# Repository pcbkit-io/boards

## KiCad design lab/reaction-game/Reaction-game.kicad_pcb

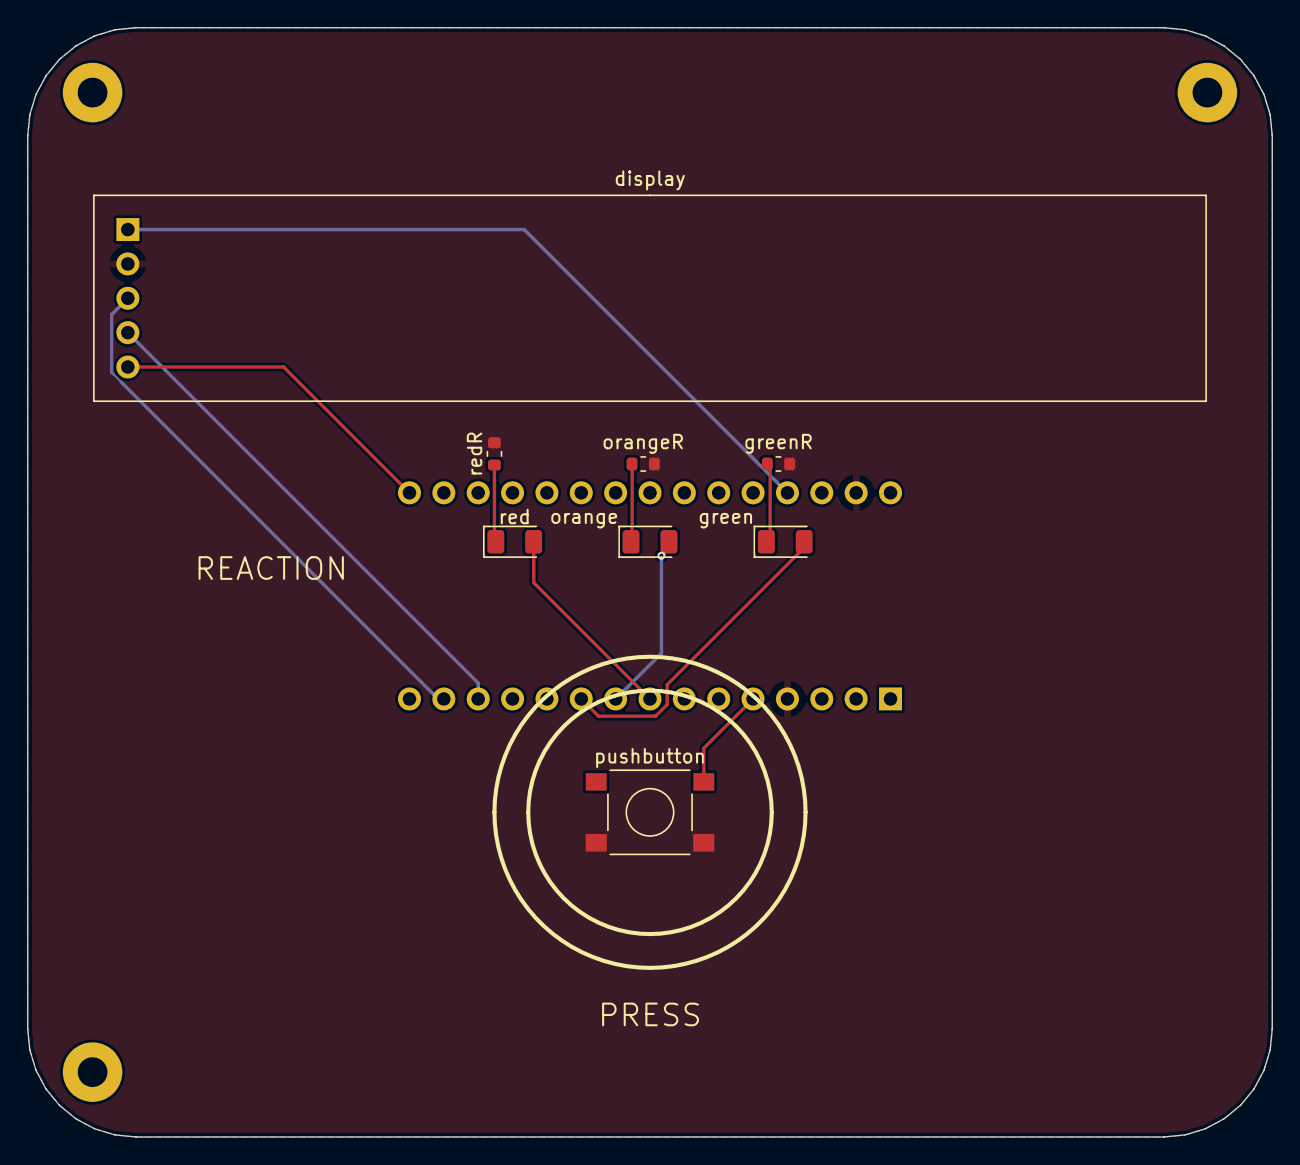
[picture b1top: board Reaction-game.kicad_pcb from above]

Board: 2 copper layers, 92.0 x 82.0 mm, 12 parts (1 on the bottom side), 12 nets.

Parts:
H1, H2, H3: MountingHole_2.2mm_M2_Pad
U1: A000005; Arduino_Nano_Socket_2x15_P2.54mm_W15.24mm
display: MAX7219 8-digit 7-segment LED display module; MAX7219_8digit_Module_Socket_1x05_P2.54mm
green: green; LED_1206_3216Metric
greenR: 1kohm; R_0603_1608Metric
orange: orange; LED_1206_3216Metric
orangeR: 1kohm; R_0603_1608Metric
pushbutton: PTS645SM43SMTR92 LFS; SW_Tactile_SPST_6x6mm_SMD
red: red; LED_1206_3216Metric
redR: 1kohm; R_0603_1608Metric

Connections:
GND: U1.4 (GND), U1.29 (GND), display.2 (GND), greenR.2 (b), orangeR.2 (b), pushbutton.2 (b), redR.2 (b)
GREEN: U1.10 (D7), green.2 (A)
GREEN_K: green.1 (K), greenR.1 (a)
LOAD: U1.13 (D10), display.4 (CS)
MOSI: U1.14 (D11), display.3 (DIN)
ORANGE: U1.9 (D6), orange.2 (A)
ORANGE_K: orange.1 (K), orangeR.1 (a)
PRESS: U1.5 (D2), pushbutton.1 (a)
RED: U1.8 (D5), red.2 (A)
RED_K: red.1 (K), redR.1 (a)
SCK: U1.16 (D13), display.5 (CLK)
V5: U1.27 (P5V), display.1 (VCC)

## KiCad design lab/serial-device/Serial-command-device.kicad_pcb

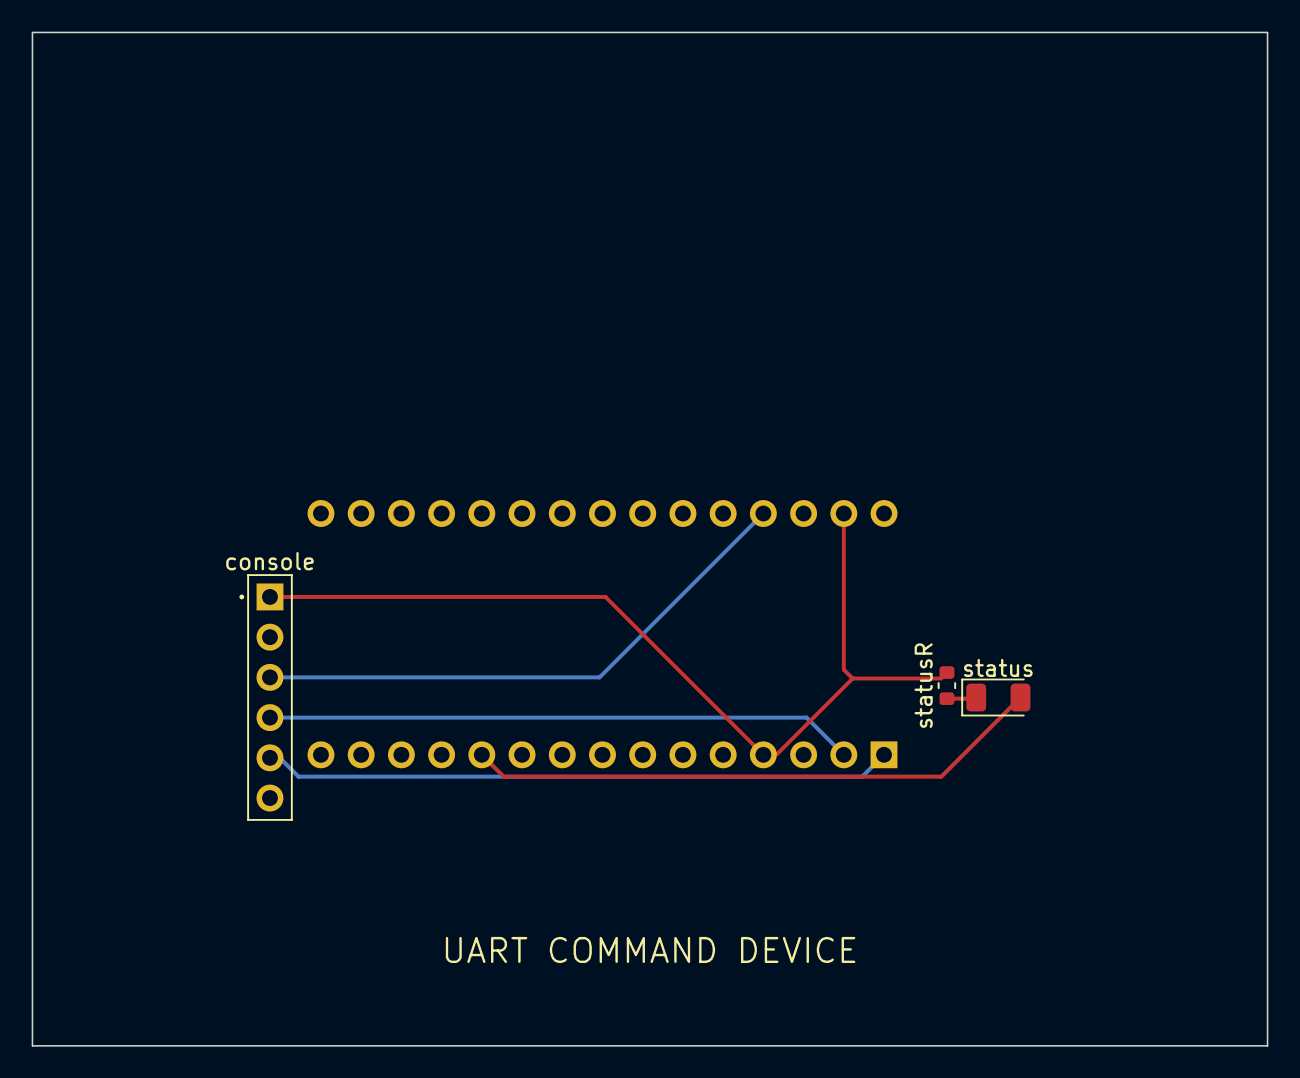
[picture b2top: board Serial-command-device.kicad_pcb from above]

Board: 2 copper layers, 78.0 x 64.0 mm, 4 parts (1 on the bottom side), 6 nets.

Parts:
U1: A000005; Arduino_Nano_Socket_2x15_P2.54mm_W15.24mm
console: PinHeader_1x06_P2.54mm_Vertical
status: green; LED_1206_3216Metric
statusR: 1kohm; R_0603_1608Metric

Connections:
GND: U1.4 (GND), U1.29 (GND), console.1, statusR.2 (b)
LIGHT: U1.11 (D8), status.2 (A)
LIGHT_K: status.1 (K), statusR.1 (a)
RX: U1.2 (D0), console.4
TX: U1.1 (D1), console.5
V5: U1.27 (P5V), console.3

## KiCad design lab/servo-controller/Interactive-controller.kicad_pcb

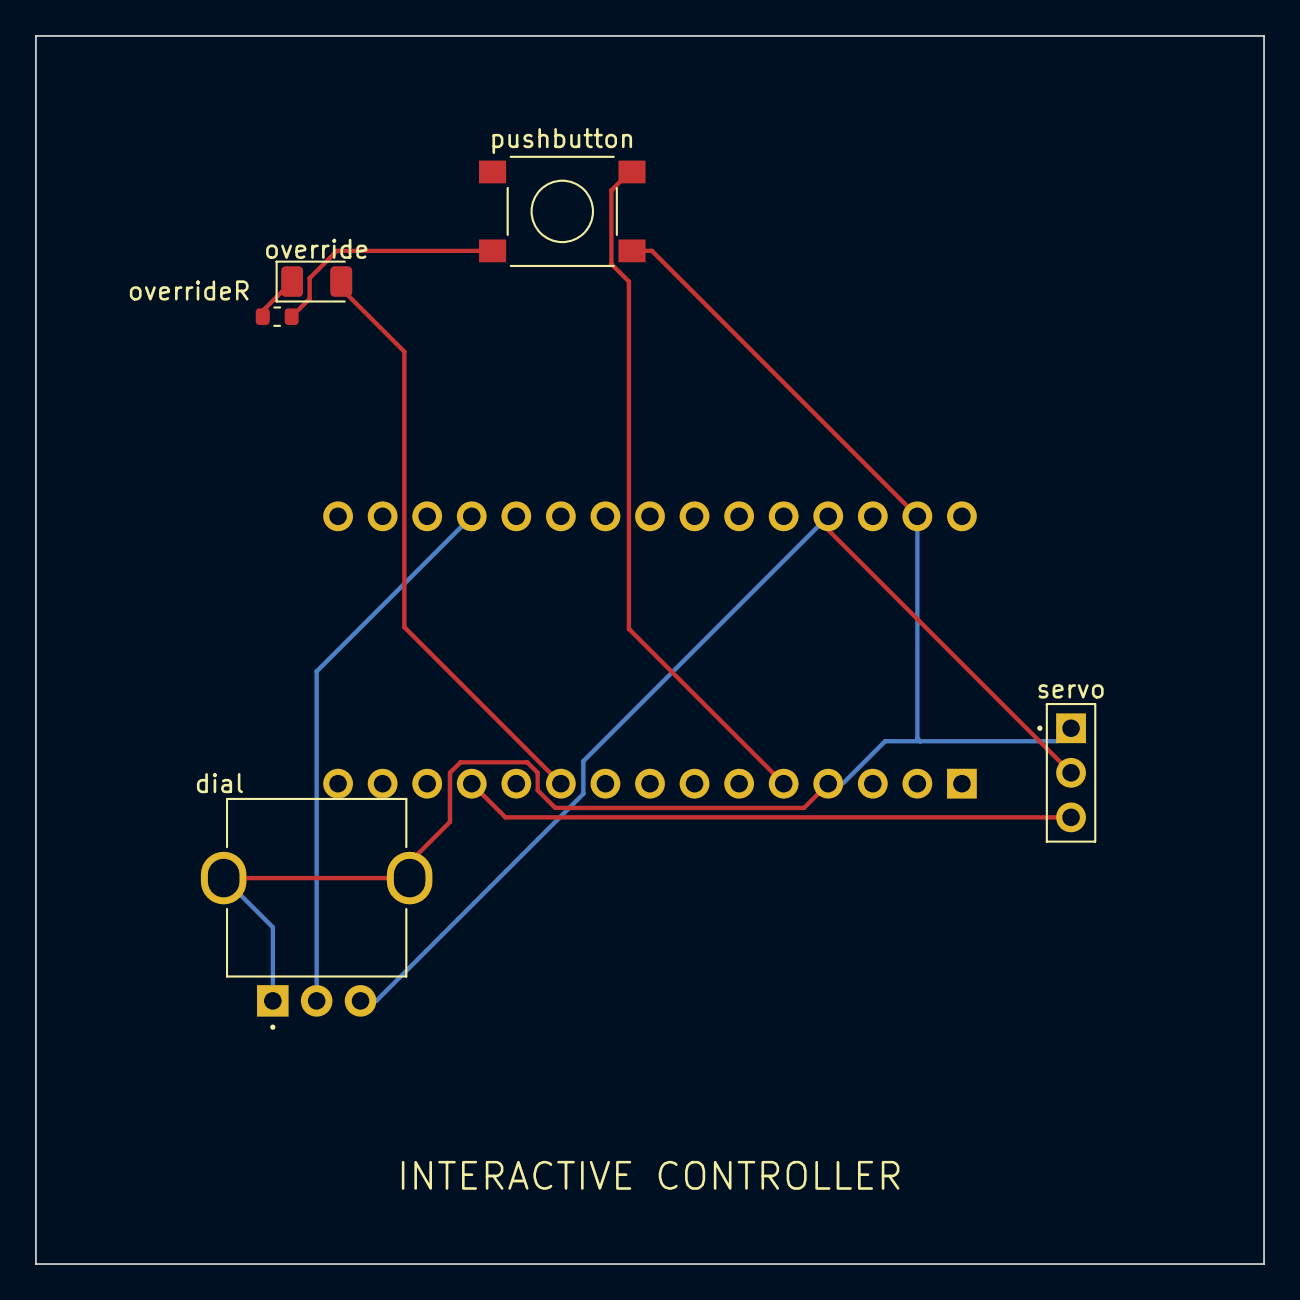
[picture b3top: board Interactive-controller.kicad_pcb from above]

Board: 2 copper layers, 70.0 x 70.0 mm, 6 parts (1 on the bottom side), 7 nets.

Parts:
U1: A000005; Arduino_Nano_Socket_2x15_P2.54mm_W15.24mm
dial: PTV09A-4020F-B103; Potentiometer_Bourns_PTV09A-4_Vertical
override: green; LED_1206_3216Metric
overrideR: 1kohm; R_0603_1608Metric
pushbutton: PTS645SM43SMTR92 LFS; SW_Tactile_SPST_6x6mm_SMD
servo: RC servo header, 1 x 3 pins, 2.54 mm; PinHeader_1x03_P2.54mm_Vertical

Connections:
ANALOG: U1.19 (A0), dial.2 (W)
BUTTON: U1.5 (D2), pushbutton.1 (a)
GND: U1.4 (GND), U1.29 (GND), dial.1 (CCW), dial.MP, overrideR.1 (a), pushbutton.2 (b), servo.1 (GND)
OVERRIDE: U1.10 (D7), override.2 (A)
OVERRIDE_K: override.1 (K), overrideR.2 (b)
SERVO: U1.12 (D9), servo.3 (SIG)
V5: U1.27 (P5V), dial.3 (CW), servo.2 (VPLUS)

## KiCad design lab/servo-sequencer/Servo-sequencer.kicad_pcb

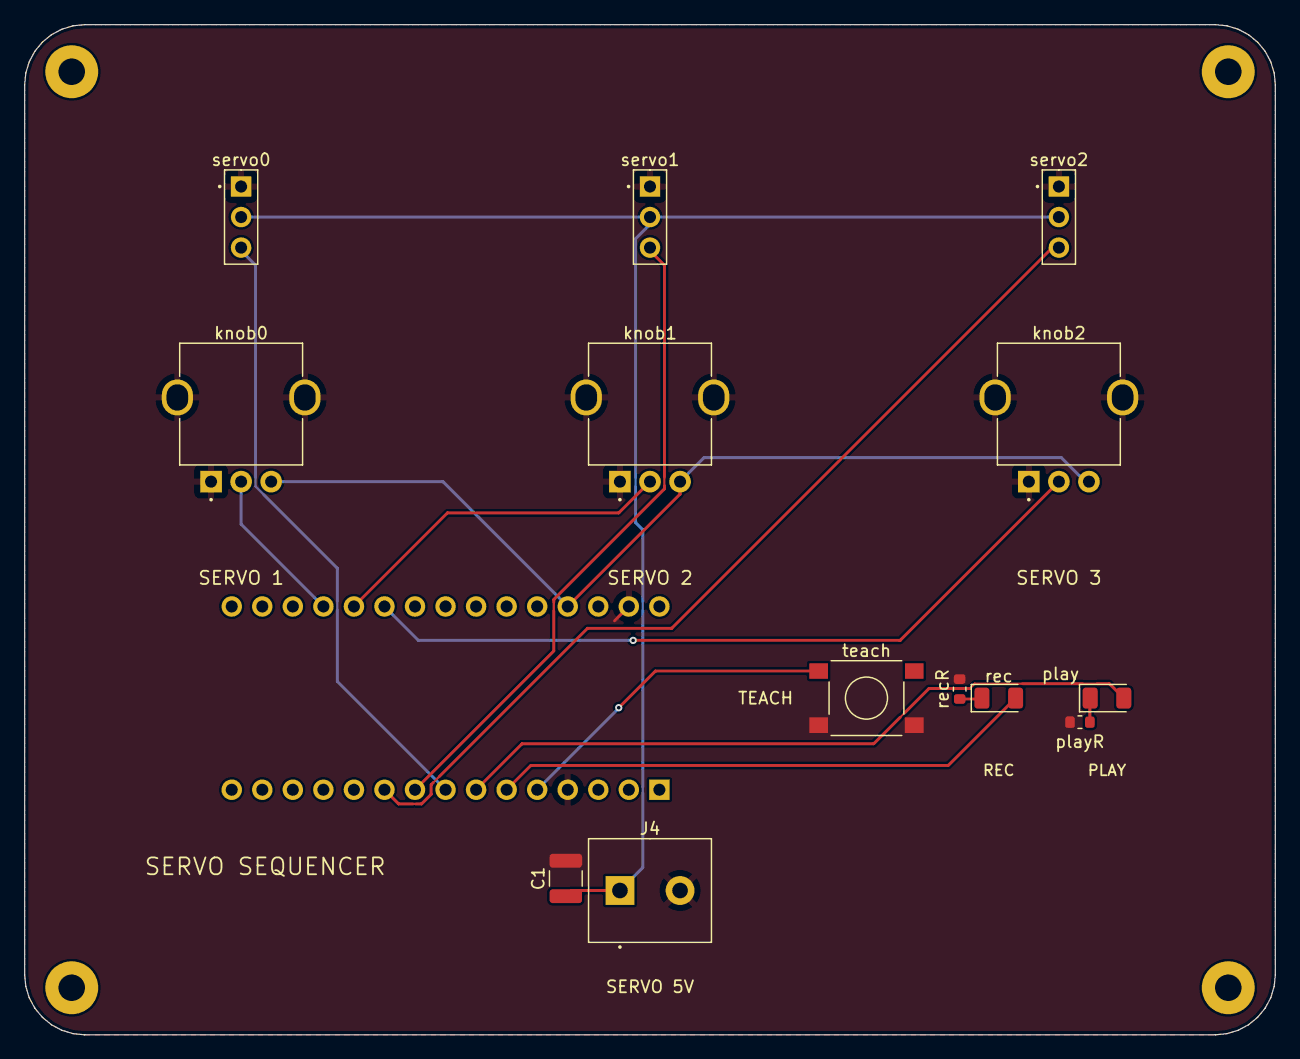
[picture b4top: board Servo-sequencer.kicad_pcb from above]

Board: 2 copper layers, 104.0 x 84.0 mm, 18 parts (1 on the bottom side), 14 nets.

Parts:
C1: 100uF; C_1210_3225Metric
H1, H2, H3, H4: MountingHole_2.2mm_M2_Pad
J4: 5 V 2 A; TerminalBlock_1x02_P5.00mm
U1: A000005; Arduino_Nano_Socket_2x15_P2.54mm_W15.24mm
knob0, knob1, knob2: PTV09A-4020F-B103; Potentiometer_Bourns_PTV09A-4_Vertical
play: green; LED_1206_3216Metric
playR: 1kohm; R_0603_1608Metric
rec: red; LED_1206_3216Metric
recR: 1kohm; R_0603_1608Metric
servo0, servo1, servo2: RC servo header, 1 x 3 pins, 2.54 mm; PinHeader_1x03_P2.54mm_Vertical
teach: PTS645SM43SMTR92 LFS; SW_Tactile_SPST_6x6mm_SMD

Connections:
GND: C1.2 (b), J4.2, U1.4 (GND), U1.29 (GND), knob0.1 (CCW), knob0.MP, knob1.1 (CCW), knob1.MP, knob2.1 (CCW), knob2.MP, playR.2 (b), recR.2 (b), servo0.1 (GND), servo1.1 (GND), servo2.1 (GND), teach.2 (b)
KNOB0: U1.19 (A0), knob0.2 (W)
KNOB1: U1.20 (A1), knob1.2 (W)
KNOB2: U1.21 (A2), knob2.2 (W)
PLAY: U1.7 (D4), play.2 (A)
PLAY_K: play.1 (K), playR.1 (a)
REC: U1.6 (D3), rec.2 (A)
REC_K: rec.1 (K), recR.1 (a)
SERVO0: U1.8 (D5), servo0.3 (SIG)
SERVO1: U1.9 (D6), servo1.3 (SIG)
SERVO2: U1.10 (D7), servo2.3 (SIG)
TEACH: U1.5 (D2), teach.1 (a)
V5: U1.27 (P5V), knob0.3 (CW), knob1.3 (CW), knob2.3 (CW)
VSERVO: C1.1 (a), J4.1, servo0.2 (VPLUS), servo1.2 (VPLUS), servo2.2 (VPLUS)

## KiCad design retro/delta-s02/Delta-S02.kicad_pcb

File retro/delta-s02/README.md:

# Delta-S02

**Дельта-С-02**, the ZX Spectrum 48K compatible home computer made by Elara in Cheboksary in 1993,
as its factory documents draw it: «Схема электрическая принципиальная БПК Дельта-С» (Приложение 5
of its manual) for the circuit, «Плата процессора БПК Дельта-С-02» (Приложение 6) for where every
part sits on its 285 × 150 mm board. 52 Soviet chips and no ULA: the picture, the memory's
RAS/CAS timing and the frame interrupt are made by counters and gates.

Open it at **https://app.pcbkit.io/github/pcbkit-io/boards/tree/main/retro/delta-s02** and run it:
the board runs as it is wired, chip by chip (ADR 0043): a Z80A on its pins, eight КР565РУ5В
DRAMs behind their multiplexers, the КМ573РФ8А with the standard 48K ROM, the КР1533 and К555 logic
with their datasheets' delays. A television on the RGB socket XS9 scans the board's own sync and
colour lines, shown in the laboratory's output (`tv.js` draws the set around the picture); the
keyboard on XS2/XS3 takes your keys and the joysticks on XS6 (Kempston) and XS8 (Sinclair) your
first and second gamepad (`input.js` maps them: operate the device, then type `J`, `"`, `"`, Enter
for `LOAD ""`); the cassette recorder on XS7 holds The Scorched Earth (X-Project
Association, 1997, freeware): press play on the cassette (the laboratory's Plugged in) to load it as
the board does (about two minutes of the board's time, much longer in a browser: every chip runs
at every nanosecond), or **Skip loading** to resume the board as that tape leaves it, saved on this
board with this ROM (a release asset beside the cassette): the game's menu at once.

| Part | What it is |
|---|---|
| DD44 | Z80A (КР1858ВМ1 class), 3.5 MHz from the 14 MHz crystal BQ1 through DD6 |
| DD41 | КМ573РФ8А, the 48K ROM |
| DD25–DD28, DD31–DD34 | КР565РУ5В, 64 K × 1 DRAM each, one per data bit |
| DD3, DD4, DD14 | the line counter: 464 dots of 7 MHz a line |
| DD20, DD21, DD7 | the frame counter (313 lines) and the FLASH divider |
| DD24, DD30, DD35, DD36, DD17 | the RAM address multiplexers: the CPU's and the picture's, row and column |
| DD38–DD40, DD51, DD52, DD50, DD49 | pixel shift registers, attribute and border registers, colour |
| DD42, DD43, DD45, DD48, DD46 | address, data and control buffers |
| DD47, DD15, DD16 | port #FE (border, beeper, tape out), keyboard and Kempston joystick |
| DA1 | К554СА3А, the tape input's comparator |
| XS5 … XS9, XP1 | power, Kempston, tape, Sinclair joystick, RGB; the system connector |

Not simulated: the RF modulator in its can (VT1, L2) and the transistor buffers of the RGB socket;
the television reads the colour lines behind them. The modulator's output goes by a coaxial cable
from the pads XS4 to the aerial socket (САТ-Г) on the case. The keyboard itself (a membrane on a steel
plate) is off the board, on the flat cables at XS2 and XS3.

The board is placed as the factory's drawing places it and routed by PCBKit (two layers, every net,
no errors). The parts are Soviet and long out of production; the board can be ordered,
and the chips' equivalents (74ALS, 74LS, 4164, 27128, Z80) fit their 2.5 mm metric sockets only
with bent legs: the metric pitch is the original's.

Sources: zx-pk.ru (the factory sheet scanned by crackown, 2022), the Omsk archive of Andrey
Pikalo (connector pinouts), research notes in PCBKit's `research/delta-s02-2026-10-26.md`.

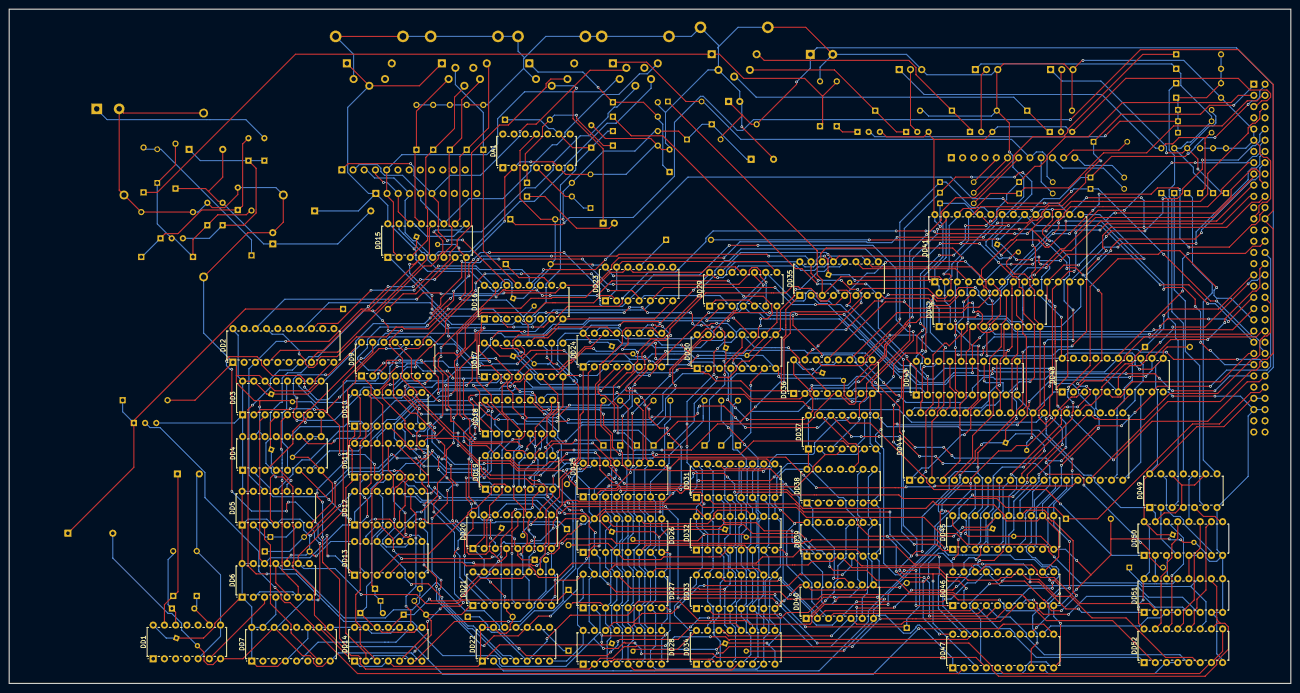
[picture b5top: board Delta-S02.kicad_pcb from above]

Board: 2 copper layers, 285.5 x 150.2 mm, 186 parts (0 on the bottom side), 242 nets.

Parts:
BQ1: 14MHz; Crystal_HC49-U
C1, C8, C9, C10, C11, C14, C15, C16, C17, C22, C23, C24, C25, C26, C27, C28, C29, C30, C33: 100nF; C_KM6_Under_DIP
C2: 300pF; C_KM_P5mm_W6mm
C3: 68nF; C_KM_P5mm_W6mm
C4, C5: 15pF; C_KM_P5mm_W6mm
C6: 110pF; C_KM_P5mm_W6mm
C7: 18pF; C_KM_P5mm_W6mm
C12: 33nF; C_KM_P5mm_W6mm
C13: 330pF; C_KM_P5mm_W6mm
C18: 330pF; C_KM_P2.5mm_W4mm
C19: 4.7uF; CP_K50_D5mm_H11mm_P2.5mm
C21: 6.8nF; C_KM_P5mm_W6mm
C31: 10uF; CP_K50_D6mm_H11mm_P2.5mm
C32: 470uF; CP_K50_D10mm_H20mm_P5mm
C44: 47pF; C_KM_P5mm_W6mm
C50: 10uF; CP_K50_D5mm_H11mm_P2.5mm
DA1: К554СА3А; DIP-14_W7.5mm_P2.5mm
DD1, DD9, DD13: КР1533ЛН1; DIP-14_W7.5mm_P2.5mm
DD2, DD42, DD43, DD46, DD47, DD48: КР1533ИР22; DIP-20_W7.5mm_P2.5mm
DD3, DD4, DD7, DD20, DD21: КР1533ИЕ7; DIP-16_W7.5mm_P2.5mm
DD5, DD6, DD14, DD22: КР1533ТМ2; DIP-14_W7.5mm_P2.5mm
DD10, DD19, DD23, DD29: КР1533ЛЛ1; DIP-14_W7.5mm_P2.5mm
DD11: КР1533ЛА4; DIP-14_W7.5mm_P2.5mm
DD12: КР1533ЛИ1; DIP-14_W7.5mm_P2.5mm
DD15, DD16, DD17, DD24, DD30, DD35, DD36, DD50: КР1533КП11А; DIP-16_W7.5mm_P2.5mm
DD18: КР1533ЛА3; DIP-14_W7.5mm_P2.5mm
DD25, DD26, DD27, DD28, DD31, DD32, DD33, DD34: КР565РУ5В; DIP-16_W7.5mm_P2.5mm
DD37, DD49: КР1533ЛП5; DIP-14_W7.5mm_P2.5mm
DD38, DD39, DD40: К555ИР16; DIP-14_W7.5mm_P2.5mm
DD41: КМ573РФ8А; DIP-28_W15mm_P2.5mm
DD44: Z80A; DIP-40_W15mm_P2.5mm
DD45: КР1533АП6; DIP-20_W7.5mm_P2.5mm
DD51, DD52: КР1533КП13; DIP-16_W7.5mm_P2.5mm
DR1: НР1-4-9 10 кОм; R_Array_HR1-4-9_10
E1: Экран модулятора; Shield_Can_35.5x36.5mm
HA1: ЗП-3; Buzzer_ZP-3
L1: ДМ-0,2 100 мкГн; L_DM_P12.5mm
L2: 7 вит. ПЭТВ-2 0,535; L_Air_7T_D6.5mm
R1, R11, R12, R65: 510ohm; R_MLT-0.125_P10mm
R2, R52: 5.6kohm; R_MLT-0.125_P10mm
R3, R58, R59, R60: 2.7kohm; R_MLT-0.125_P10mm
R7, R25, R30, R32: 1kohm; R_MLT-0.125_P10mm
R9, R43, R46, R48, R50: 220ohm; R_MLT-0.125_P10mm
R10, R15, R16, R17, R18, R19, R20, R51, R55, R56, R57, R61, R64: 470ohm; R_MLT-0.125_P10mm
R13, R21, R22, R26, R42, R62, R63: 10kohm; R_MLT-0.125_P10mm
R23, R27, R28, R29, R34, R35, R36, R37, R38, R39, R40, R41: 22ohm; R_MLT-0.125_P10mm
R24: 160kohm; R_MLT-0.125_P10mm
R31: 1.5kohm; R_MLT-0.125_P10mm
R33: 240ohm; R_MLT-0.125_P10mm
R44: 100ohm; R_MLT-0.125_P10mm
R45, R47, R49: СП3-38б 22 кОм; Trimmer_SP3
R53: 1.3kohm; R_MLT-0.125_P10mm
R54: 3kohm; R_MLT-0.125_P10mm
SB1: КМ1-1; Button_KM1-1
VD1, VD2, VD4, VD5, VD6, VD11, VD14, VD15, VD17, VD18, VD19, VD20, VD21, VD22, VD23, VD24, VD25: КД522Б; D_KD522_P7.5mm
VD3: КС119А; D_KD522_P7.5mm
VT1: КТ316БМ; KT-26
VT3, VT4, VT5, VT6, VT7: КТ3102БМ; KT-26
XP1: СНП59-64/94-11В-23-2; Connector_SNP59-64_2x32
XS2, XS3: ОНП-СГ-83-12; Socket_ONP-SG-83_1x12
XS4: РК-75 к гнезду САТ-Г; Cable_Coax_Pads
XS5, XS7, XS9: ОНЦ-ВГ-4-5/16-Р; DIN_ONC-VG_5
XS6, XS8: ОНЦ-ВГ-11-7/16-Р; DIN_ONC-VG_7

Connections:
A0: DD19.9 (A3), DD36.5 (A2), DD41.10 (A0), DD42.12 (Q4), XP1.A8
A1: DD10.10 (B3), DD18.2 (B1), DD36.2 (A1), DD41.9 (A1), DD42.9 (Q3), XP1.A9
A2: DD36.14 (A4), DD41.8 (A2), DD43.12 (Q4), XP1.A10
A3: DD36.11 (A3), DD41.7 (A3), DD42.15 (Q5), XP1.A11
A4: DD35.2 (A1), DD41.6 (A4), DD43.15 (Q5), XP1.A23
A5: DD18.1 (A1), DD23.5 (B2), DD35.5 (A2), DD41.5 (A5), DD42.16 (Q6), XP1.A22
A6: DD35.11 (A3), DD41.4 (A6), DD43.16 (Q6), XP1.A21
A7: DD35.14 (A4), DD41.3 (A7), DD43.5 (Q1), XP1.A20
A8: DD36.6 (B2), DD41.25 (A8), DD43.2 (Q0), VD19.1 (K), XP1.B25
A9: DD36.3 (B1), DD41.24 (A9), DD43.19 (Q7), VD15.1 (K), XP1.A26
A10: DD36.13 (B4), DD41.21 (A10), DD42.6 (Q2), VD14.1 (K), XP1.B26
A11: DD36.10 (B3), DD41.23 (A11), DD43.6 (Q2), VD11.1 (K), XP1.A27
A12: DD35.3 (B1), DD41.2 (A12), DD42.2 (Q0), VD4.1 (K), VD21.1 (K), XP1.A2
A13: DD35.6 (B2), DD41.26 (A13), DD42.19 (Q7), VD20.1 (K), XP1.B2
A14: DD29.12 (A4), DD35.10 (B3), DD42.5 (Q1), VD17.1 (K), XP1.A1
A15: DD29.13 (B4), DD35.13 (B4), DD43.9 (Q3), VD18.1 (K), XP1.B1
A1415: DD13.11 (A5), DD23.12 (A4), DD29.11 (Y4)
AT0: DD50.2 (A1), DD51.15 (QA)
AT1: DD50.3 (B1), DD51.14 (QB)
AT2: DD51.13 (QC), VD22.1 (K)
AT3: DD50.5 (A2), DD50.6 (B2), DD51.12 (QD)
AT4: DD50.13 (B4), DD52.15 (QA)
AT5: DD50.14 (A4), DD52.14 (QB)
AT6: DD50.11 (A3), DD52.13 (QC)
AT7: DD50.10 (B3), DD52.12 (QD)
BC: C18.2 (b), DD10.1 (A1), DD11.1 (A1), DD14.2 (D1), DD14.6 (QN1)
BEEP: DD47.2 (Q0), VT3.2 (B)
BEEPE: HA1.1, R10.1 (a), R23.1 (a), VT3.1 (E)
BLANK: DD37.8 (Y3), DD49.1 (A1), DD49.4 (A2), DD49.9 (A3), DD49.12 (A4), DD50.15 (OE)
BRD0: DD47.12 (Q4), DD51.3 (A1), DD51.4 (B1)
BRD1: DD47.9 (Q3), DD52.3 (A1), DD52.4 (B1)
BRD2: DD47.5 (Q1), DD52.7 (D1), DD52.9 (C1)
CB: DD49.2 (B1), DD50.4 (Y1)
CG: DD49.5 (B2), DD50.9 (Y3)
CI: DD49.13 (B4), DD50.7 (Y2)
CLK14: DD1.6 (Y3), DD6.3 (CLK1)
CO3: DD3.12 (CO), DD4.5 (UP)
CO20: DD20.12 (CO), DD21.5 (UP)
CR: DD49.10 (B3), DD50.12 (Y4)
CSRAM: DD9.4 (Y2), DD22.3 (CLK1)
CVE: R44.1 (a), VT4.1 (E)
D0: DD2.3 (D0), DD5.12 (D2), DD15.4 (Y1), DD25.2 (DIN), DD41.11 (O0), DD45.12 (B7), DD46.12 (Q4), DD47.13 (D4), XP1.B5
D1: DD2.4 (D1), DD15.12 (Y4), DD26.2 (DIN), DD41.12 (O1), DD45.11 (B8), DD46.9 (Q3), DD47.8 (D3), XP1.B6
D2: DD2.7 (D2), DD15.7 (Y2), DD27.2 (DIN), DD41.13 (O2), DD45.14 (B5), DD46.15 (Q5), DD47.4 (D1), XP1.B7
D3: DD2.8 (D3), DD15.9 (Y3), DD28.2 (DIN), DD41.15 (O3), DD45.17 (B2), DD46.19 (Q7), DD47.18 (D7), XP1.B10
D4: DD2.13 (D4), DD16.12 (Y4), DD31.2 (DIN), DD41.16 (O4), DD45.18 (B1), DD46.2 (Q0), DD47.3 (D0), XP1.B11
D5: DD2.14 (D5), DD16.4 (Y1), DD32.2 (DIN), DD41.17 (O5), DD45.16 (B3), DD46.5 (Q1), XP1.B12
D6: DD2.17 (D6), DD16.7 (Y2), DD33.2 (DIN), DD41.18 (O6), DD45.15 (B4), DD46.16 (Q6), XP1.B8
D7: DD2.18 (D7), DD16.9 (Y3), DD34.2 (DIN), DD41.19 (O7), DD45.13 (B6), DD46.6 (Q2), XP1.B3
DB: R45.1 (E1), R55.2 (b), R58.1 (a), VD25.2 (A)
DG: R47.1 (E1), R52.1 (a), R56.2 (b), R59.1 (a), VD24.2 (A)
DR: R49.1 (E1), R57.2 (b), R60.1 (a), VD23.2 (A)
EAR: C44.1 (a), DA1.9 (OUT), DD16.5 (A2), R24.1 (a), R32.1 (a)
F: DD5.2 (D1), DD5.6 (QN1), VD1.1 (K)
F7: DD6.5 (Q1), DD6.11 (CLK2), DD38.9 (CLK), DD39.9 (CLK), DD40.9 (CLK)
F7N: DD3.5 (UP), DD6.2 (D1), DD6.6 (QN1)
FC: DD4.12 (CO), DD10.2 (B1), DD14.3 (CLK1)
FF: C12.1 (a), DD12.12 (A4), DD14.8 (QN2), DD14.12 (D2)
FL16: DD5.3 (CLK1), DD7.7 (QD)
FLN: DD37.12 (A4), R13.1 (a), VD1.2 (A), VD22.2 (A)
FV6: DD11.11 (C3), DD12.11 (Y4)
GND: C1.2 (b), C3.2 (b), C5.2 (b), C8.2 (b), C9.2 (b), C10.2 (b), C11.2 (b), C13.2 (b), C14.2 (b), C15.2 (b), C16.2 (b), C17.2 (b), C21.2 (b), C22.2 (b), C23.2 (b), C24.2 (b), C25.2 (b), C26.2 (b), C27.2 (b), C28.2 (b), C29.2 (b), C30.2 (b), C31.2 (b), C32.2 (b), C33.2 (b), C44.2 (b), C50.2 (b), DA1.2 (GND), DA1.6 (VEE), DD1.7 (GND), DD2.1 (OE), DD2.10 (GND), DD3.8 (GND), DD3.14 (CLR), DD4.8 (GND), DD4.9 (D), DD4.10 (C), DD4.14 (CLR), DD4.15 (A), DD5.7 (GND), DD6.7 (GND), DD7.8 (GND), DD7.14 (CLR), DD9.7 (GND), DD10.7 (GND), DD11.7 (GND), DD12.7 (GND), DD13.7 (GND), DD14.7 (GND), DD15.8 (GND), DD16.8 (GND), DD17.8 (GND), DD17.10 (B3), DD17.15 (OE), DD18.7 (GND), DD19.7 (GND), DD20.1 (B), DD20.8 (GND), DD20.10 (C), DD20.14 (CLR), DD20.15 (A), DD21.1 (B), DD21.8 (GND), DD21.9 (D), DD21.14 (CLR), DD21.15 (A), DD22.7 (GND), DD23.7 (GND), DD24.3 (B1), DD24.8 (GND), DD25.16 (GND), DD26.16 (GND), DD27.16 (GND), DD28.16 (GND), DD29.7 (GND), DD30.8 (GND), DD30.10 (B3), DD31.16 (GND), DD32.16 (GND), DD33.16 (GND), DD34.16 (GND), DD35.8 (GND), DD36.8 (GND), DD37.7 (GND), DD38.6 (MODE), DD38.7 (GND), DD39.1 (SER), DD39.7 (GND), DD40.7 (GND), DD41.14 (GND), DD41.22 (OE), DD42.1 (OE), DD42.10 (GND), DD43.1 (OE), DD43.10 (GND), DD44.29 (GND), DD45.10 (GND), DD45.19 (OE), DD46.10 (GND), DD47.1 (OE), DD47.10 (GND), DD48.1 (OE), DD48.10 (GND), DD49.7 (GND), DD50.8 (GND), DD51.7 (D1), DD51.8 (GND), DD51.9 (C1), DD52.8 (GND), E1.1 (GND), E1.2 (GND), E1.3 (GND), E1.4 (GND), HA1.2, R1.2 (b), R3.2 (b), R10.2 (b), R15.2 (b), R16.2 (b), R17.2 (b), R18.2 (b), R19.2 (b), R20.2 (b), R30.2 (b), R33.2 (b), R43.2 (b), R45.3 (E2), R46.2 (b), R47.3 (E2), R48.2 (b), R49.3 (E2), R50.2 (b), R54.2 (b), R58.2 (b), R59.2 (b), R60.2 (b), R64.2 (b), SB1.2, VD2.2 (A), VD3.2 (A), XP1.A5, XP1.A6, XP1.A13, XP1.A30, XP1.B30, XS4.2 (GND), XS5.2 (C2), XS5.S1 (S), XS5.S2 (S), XS6.S1 (S), XS6.S2 (S), XS7.2 (C2), XS7.S1 (S), XS7.S2 (S), XS8.S1 (S), XS8.S2 (S), XS9.2 (C2), XS9.S1 (S), XS9.S2 (S)
HS: DD10.6 (Y2), DD37.4 (A2)
INFU: DD37.13 (B4), DD38.10 (QD)
INKSEL: DD37.11 (Y4), DD50.1 (S)
IOUT: DD19.12 (A4), R64.1 (a), XP1.B28
J1: DD15.13 (B4), R16.1 (a), XS6.2 (C2)
J2: DD15.3 (B1), R17.1 (a), XS6.3 (C3)
J3: DD15.6 (B2), R18.1 (a), XS6.4 (C4)
J4: DD15.10 (B3), R19.1 (a), XS6.5 (C5)
J5: DD16.13 (B4), R20.1 (a), XS6.6 (C6)
KA8: VD19.2 (A), XS3.10 (C10)
KA9: VD15.2 (A), XS3.7 (C7)
KA10: VD14.2 (A), XS3.6 (C6)
KA11: VD11.2 (A), XS3.5 (C5)
KA12: VD4.2 (A), VD21.2 (A), XS3.8 (C8), XS8.1 (C1)
KA13: VD20.2 (A), XS3.9 (C9)
KA14: VD17.2 (A), XS3.11 (C11)
KA15: VD18.2 (A), XS3.12 (C12)
KC: C12.2 (b), DD9.1 (A1), R15.1 (a), VD2.1 (K)
KL0: DD15.2 (A1), DR1.2 (R1), XS2.5 (C5), XS8.2 (C2)
KL1: DD15.14 (A4), DR1.3 (R2), XS2.4 (C4), XS8.3 (C3)
KL2: DD15.5 (A2), DR1.4 (R3), XS2.3 (C3), XS8.4 (C4)
KL3: DD15.11 (A3), DR1.5 (R4), XS2.2 (C2), XS8.5 (C5)
KL4: DD16.14 (A4), DR1.6 (R5), XS2.1 (C1), XS8.6 (C6)
KSEL: DD15.1 (S), DD16.1 (S), DD18.3 (Y1)
M0: DD3.3 (QA), DD6.12 (D2), DD11.4 (B2), DD12.1 (A1)
M1: DD3.2 (QB), DD11.3 (A2), DD13.9 (A4), DD35.15 (OE), DD36.15 (OE)
M2: DD3.6 (QC), DD10.12 (A4), DD17.1 (S), DD19.1 (A1), DD51.11 (CLK), DD52.11 (CLK)
M3: DD3.7 (QD), DD30.5 (A2)
M4: DD4.3 (QA), DD30.14 (A4)
M5: DD4.2 (QB), DD10.5 (B2), DD30.2 (A1)
M6: DD4.6 (QC), DD13.1 (A1), DD24.5 (A2)
M7: DD4.7 (QD), DD11.13 (C1), DD24.14 (A4)
M8: DD17.4 (Y1), DD30.6 (B2)
M9: DD17.7 (Y2), DD30.13 (B4)
M10: DD17.9 (Y3), DD30.3 (B1)
M11: DD17.12 (Y4), DD24.13 (B4)
M12: DD10.11 (Y4), DD24.6 (B2)
MA0: DD30.7 (Y2), DD36.7 (Y2), R41.1 (a)
MA1: DD30.12 (Y4), DD36.4 (Y1), R39.1 (a)
MA2: DD30.4 (Y1), DD36.12 (Y4), R40.1 (a)
MA3: DD24.7 (Y2), DD36.9 (Y3), R35.1 (a)
MA4: DD24.12 (Y4), DD35.4 (Y1), R36.1 (a)
MA5: DD24.4 (Y1), DD35.7 (Y2), R37.1 (a)
MA6: DD24.9 (Y3), DD35.9 (Y3), R34.1 (a)
MA7: DD30.9 (Y3), DD35.12 (Y4), R38.1 (a)
MD0: DD25.14 (DOUT), DD39.2 (A), DD46.13 (D4), DD51.1 (B2)
MD1: DD26.14 (DOUT), DD39.3 (B), DD46.8 (D3), DD52.2 (A2)
MD2: DD27.14 (DOUT), DD39.4 (C), DD46.14 (D5), DD52.6 (D2)
MD3: DD28.14 (DOUT), DD39.5 (D), DD46.18 (D7), DD51.2 (A2)
MD4: DD31.14 (DOUT), DD40.2 (A), DD46.3 (D0), DD52.1 (B2)
MD5: DD32.14 (DOUT), DD40.3 (B), DD46.4 (D1), DD52.5 (C2)
MD6: DD33.14 (DOUT), DD40.4 (C), DD46.17 (D6), DD51.6 (D2)
MD7: DD34.14 (DOUT), DD40.5 (D), DD46.7 (D2), DD51.5 (C2)
MICN: C21.1 (a), R30.1 (a), R31.2 (b), XS7.1 (C1)
MICO: DD47.19 (Q7), R31.1 (a)
MIX: R51.2 (b), R52.2 (b), R53.2 (b), R54.1 (a), VD23.1 (K), VD24.1 (K), VD25.1 (K), VT4.2 (B)
OB: R46.1 (a), VT5.1 (E), XS9.4 (C4)
OG: R48.1 (a), VT6.1 (E), XS9.5 (C5)
OR: R50.1 (a), VT7.1 (E), XS9.3 (C3)
OSC_L: BQ1.1 (X1), DD1.13 (A6), R11.1 (a)
OSC_M: C2.1 (a), DD1.12 (Y6), R11.2 (b)
OSC_N: C2.2 (b), DD1.9 (A4), R12.1 (a)
OSC_R: BQ1.2 (X2), DD1.5 (A3), DD1.8 (Y4), R12.2 (b)
P5V: C1.1 (a), C8.1 (a), C9.1 (a), C10.1 (a), C11.1 (a), C14.1 (a), C15.1 (a), C16.1 (a), C17.1 (a), C22.1 (a), C23.1 (a), C24.1 (a), C25.1 (a), C26.1 (a), C27.1 (a), C28.1 (a), C29.1 (a), C30.1 (a), C32.1 (a), C33.1 (a), DA1.11 (VCC), DD1.14 (VCC), DD2.20 (VCC), DD3.1 (B), DD3.4 (DOWN), DD3.9 (D), DD3.10 (C), DD3.11 (LOAD), DD3.15 (A), DD3.16 (VCC), DD4.1 (B), DD4.4 (DOWN), DD4.16 (VCC), DD5.1 (CLR1), DD5.4 (PRE1), DD5.10 (PRE2), DD5.13 (CLR2), DD5.14 (VCC), DD6.1 (CLR1), DD6.4 (PRE1), DD6.10 (PRE2), DD6.13 (CLR2), DD6.14 (VCC), DD7.1 (B), DD7.4 (DOWN), DD7.9 (D), DD7.10 (C), DD7.11 (LOAD), DD7.15 (A), DD7.16 (VCC), DD9.14 (VCC), DD10.14 (VCC), DD11.14 (VCC), DD12.14 (VCC), DD13.14 (VCC), DD14.1 (CLR1), DD14.4 (PRE1), DD14.10 (PRE2), DD14.13 (CLR2), DD14.14 (VCC), DD15.16 (VCC), DD16.16 (VCC), DD17.13 (B4), DD17.16 (VCC), DD18.14 (VCC), DD19.14 (VCC), DD20.4 (DOWN), DD20.16 (VCC), DD21.4 (DOWN), DD21.16 (VCC), DD22.1 (CLR1), DD22.13 (CLR2), DD22.14 (VCC), DD23.14 (VCC), DD24.10 (B3), DD24.16 (VCC), DD25.8 (VCC), DD26.8 (VCC), DD27.8 (VCC), DD28.8 (VCC), DD29.14 (VCC), DD30.16 (VCC), DD31.8 (VCC), DD32.8 (VCC), DD33.8 (VCC), DD34.8 (VCC), DD35.16 (VCC), DD36.16 (VCC), DD37.1 (A1), DD37.14 (VCC), DD38.8 (OC), DD38.14 (VCC), DD39.8 (OC), DD39.14 (VCC), DD40.8 (OC), DD40.14 (VCC), DD41.1 (VPP), DD41.27 (PGM), DD41.28 (VCC), DD42.11 (LE), DD42.20 (VCC), DD43.11 (LE), DD43.20 (VCC), DD44.11 (VCC), DD45.20 (VCC), DD46.20 (VCC), DD47.20 (VCC), DD48.11 (LE), DD48.20 (VCC), DD49.14 (VCC), DD50.16 (VCC), DD51.16 (VCC), DD52.16 (VCC), DR1.1 (COM), L1.1, R13.2 (b), R21.2 (b), R22.2 (b), R25.2 (b), R32.2 (b), R42.1 (a), R62.2 (b), R63.2 (b), R65.2 (b), VD5.1 (K), VT3.3 (C), VT4.3 (C), VT5.3 (C), VT6.3 (C), VT7.3 (C), XP1.A3, XP1.A29, XP1.B29, XS5.1 (C1), XS5.3 (C3), XS6.1 (C1)
P5V_RF: C7.2 (b), C50.1 (a), L1.2, L2.2, R2.1 (a)
PA0: DD42.13 (D4), DD44.30 (A0)
PA1: DD42.8 (D3), DD44.31 (A1)
PA2: DD43.13 (D4), DD44.32 (A2)
PA3: DD42.14 (D5), DD44.33 (A3)
PA4: DD43.14 (D5), DD44.34 (A4)
PA5: DD42.17 (D6), DD44.35 (A5)
PA6: DD43.17 (D6), DD44.36 (A6)
PA7: DD43.4 (D1), DD44.37 (A7)
PA8: DD43.3 (D0), DD44.38 (A8)
PA9: DD43.18 (D7), DD44.39 (A9)
PA10: DD42.7 (D2), DD44.40 (A10)
PA11: DD43.7 (D2), DD44.1 (A11)
PA12: DD42.3 (D0), DD44.2 (A12)
PA13: DD42.18 (D7), DD44.3 (A13)
PA14: DD42.4 (D1), DD44.4 (A14)
PA15: DD43.8 (D3), DD44.5 (A15)
PD0: DD44.14 (D0), DD45.8 (A7)
PD1: DD44.15 (D1), DD45.9 (A8)
PD2: DD44.12 (D2), DD45.6 (A5)
PD3: DD44.8 (D3), DD45.3 (A2)
PD4: DD44.7 (D4), DD45.2 (A1)
PD5: DD44.9 (D5), DD45.4 (A3)
PD6: DD44.10 (D6), DD45.5 (A4)
PD7: DD44.13 (D7), DD45.7 (A6)
PIXF: DD13.3 (A2), DD19.3 (Y1)
PORTLE: DD9.10 (Y5), DD47.11 (LE)
PORTW: DD9.11 (A5), DD19.8 (Y3)
PRSTB: DD5.11 (CLK2), DD10.8 (Y3)
R1N: DD12.2 (B1), DD13.8 (Y4), DD22.10 (PRE2), DD24.15 (OE), DD30.15 (OE)
R21N: DD16.10 (B3), R21.1 (a)
RA0: DD25.12 (A3), DD26.12 (A3), DD27.12 (A3), DD28.12 (A3), DD31.12 (A3), DD32.12 (A3), DD33.12 (A3), DD34.12 (A3), R35.2 (b)
RA1: DD25.11 (A4), DD26.11 (A4), DD27.11 (A4), DD28.11 (A4), DD31.11 (A4), DD32.11 (A4), DD33.11 (A4), DD34.11 (A4), R36.2 (b)
RA2: DD25.10 (A5), DD26.10 (A5), DD27.10 (A5), DD28.10 (A5), DD31.10 (A5), DD32.10 (A5), DD33.10 (A5), DD34.10 (A5), R37.2 (b)
RA3: DD25.13 (A6), DD26.13 (A6), DD27.13 (A6), DD28.13 (A6), DD31.13 (A6), DD32.13 (A6), DD33.13 (A6), DD34.13 (A6), R34.2 (b)
RA4: DD25.7 (A1), DD26.7 (A1), DD27.7 (A1), DD28.7 (A1), DD31.7 (A1), DD32.7 (A1), DD33.7 (A1), DD34.7 (A1), R39.2 (b)
RA5: DD25.6 (A2), DD26.6 (A2), DD27.6 (A2), DD28.6 (A2), DD31.6 (A2), DD32.6 (A2), DD33.6 (A2), DD34.6 (A2), R40.2 (b)
RA6: DD25.5 (A0), DD26.5 (A0), DD27.5 (A0), DD28.5 (A0), DD31.5 (A0), DD32.5 (A0), DD33.5 (A0), DD34.5 (A0), R41.2 (b)
RA7: DD25.9 (A7), DD26.9 (A7), DD27.9 (A7), DD28.9 (A7), DD31.9 (A7), DD32.9 (A7), DD33.9 (A7), DD34.9 (A7), R38.2 (b)
RAS: DD9.12 (Y6), DD22.11 (CLK2), DD24.1 (S), DD30.1 (S), DD35.1 (S), DD36.1 (S)
RCAS: DD25.15 (CAS), DD26.15 (CAS), DD27.15 (CAS), DD28.15 (CAS), DD31.15 (CAS), DD32.15 (CAS), DD33.15 (CAS), DD34.15 (CAS), R27.2 (b)
RDMREQ: DD23.1 (A1), DD23.13 (B4), DD29.8 (Y3)
RDRF: DD18.8 (Y3), DD19.4 (A2)
RDROM0: DD23.11 (Y4), R61.1 (a)
RFB: C3.1 (a), R2.2 (b), R3.1 (a), R9.2 (b), VD6.1 (K), VT1.2 (B)
RFC: C4.1 (a), C6.1 (a), C7.1 (a), L2.1, VT1.3 (C)
RFE: C4.2 (b), C5.1 (a), R1.1 (a), VT1.1 (E)
RFM: R7.2 (b), R9.1 (a), VD6.2 (A)
RFOUT: C6.2 (b), XS4.1 (SIG)
RRAS: DD25.4 (RAS), DD26.4 (RAS), DD27.4 (RAS), DD28.4 (RAS), DD31.4 (RAS), DD32.4 (RAS), DD33.4 (RAS), DD34.4 (RAS), R28.2 (b)
RWE: DD25.3 (WE), DD26.3 (WE), DD27.3 (WE), DD28.3 (WE), DD31.3 (WE), DD32.3 (WE), DD33.3 (WE), DD34.3 (WE), R29.2 (b)
SCR: DD13.4 (Y2), DD39.6 (MODE), DD40.6 (MODE)
SH1: DD39.10 (QD), DD40.1 (SER)
SH2: DD38.1 (SER), DD40.10 (QD)
SNDOUT: R23.2 (b), XS7.4 (C4)
SYNC: DD37.3 (Y1), R51.1 (a)
SYNCX: DD37.2 (B1), DD37.6 (Y2)
TAPEIN: C19.1 (a), XS7.3 (C3)
TBIAS: DA1.3 (INP), R24.2 (b), R25.1 (a), R33.1 (a)
TIN: DA1.4 (INN), R26.2 (b), VD3.1 (K)
TIN1: C19.2 (b), R26.1 (a)
V0: DD17.2 (A1), DD20.3 (QA)
V1: DD17.5 (A2), DD20.2 (QB)
V2: DD17.11 (A3), DD20.6 (QC)
V3: DD20.7 (QD), DD24.2 (A1)
V4: DD11.9 (A3), DD21.3 (QA), DD24.11 (A3)
V5: DD11.10 (B3), DD21.2 (QB), DD30.11 (A3)
V6: DD10.13 (B4), DD12.13 (B4), DD17.3 (B1), DD18.4 (A2), DD21.6 (QC)
V7: DD17.6 (B2), DD17.14 (A4), DD18.5 (B2), DD21.7 (QD)
VB: DD49.3 (Y1), R55.1 (a)
VG: DD49.6 (Y2), R56.1 (a)
VI: DD49.11 (Y4), R53.1 (a)
VIDEO: R7.1 (a), R43.1 (a), R44.2 (b), XS9.1 (C1)
VLD: C13.1 (a), DD14.11 (CLK2), DD18.6 (Y2), DD20.11 (LOAD), DD21.11 (LOAD)
VR: DD49.8 (Y3), R57.1 (a)
WIPB: R45.2 (W), VT5.2 (B)
WIPG: R47.2 (W), VT6.2 (B)
WIPR: R49.2 (W), VT7.2 (B)
WRBUF: DD12.3 (Y1), DD13.13 (A6), DD46.11 (LE)
WRCYC: DD19.6 (Y2), DD22.12 (D2)
Z2: DD4.11 (LOAD), DD10.3 (Y1)
nA1415: DD13.10 (Y5), DD23.2 (B1)
nBC: C18.1 (a), DD12.10 (B3), DD14.5 (Q1), DD20.5 (UP)
nBK: DD7.5 (UP), DD12.9 (A3), DD14.9 (Q2), DD20.9 (D), DD21.10 (C)
nBORDER: DD11.5 (C2), DD12.8 (Y3), DD51.10 (WS), DD52.10 (WS)
nBUSAK: DD48.5 (Q1), XP1.A25
nBUSRQ: DD44.25 (BUSRQ), R62.1 (a), XP1.A18
nCAS: DD12.6 (Y2), R27.1 (a)
nCC: DD10.4 (A2), DD11.12 (Y1), DD37.10 (B3)
nCSRAM: DD9.3 (A2), DD23.3 (Y1), DD46.1 (OE)
nINT: DD9.2 (Y1), DD44.16 (INT)
nIORC: DD19.13 (B4), DD29.6 (Y2)
nIORQ: DD29.1 (A1), DD29.5 (B2), DD48.9 (Q3), XP1.B16
nIOWC: DD10.9 (A3), DD19.10 (B3), DD23.4 (A2), DD29.3 (Y1)
nKC: DD11.8 (Y3), DD37.5 (B2), DD37.9 (A3)
nM1: DD22.2 (D1), DD44.27 (M1), DD48.3 (D0)
nM6: DD11.2 (B1), DD13.2 (Y1)
nMREQ: DD19.5 (B2), DD29.9 (A3), DD48.15 (Q5), XP1.B15
nNMI: DD44.17 (NMI), R63.1 (a), XP1.B13
nPBUSAK: DD44.23 (BUSACK), DD48.4 (D1)
nPIORQ: DD44.20 (IORQ), DD48.8 (D3)
nPMREQ: DD44.19 (MREQ), DD48.14 (D5)
nPRD: DD44.21 (RD), DD48.13 (D4)
nPWR: DD44.22 (WR), DD48.7 (D2)
nRAS: DD6.9 (Q2), DD9.13 (A6), DD44.6 (CLK), R28.1 (a), R65.1 (a)
nRD: DD18.10 (B3), DD29.4 (A2), DD29.10 (B3), DD45.1 (DIR), DD48.12 (Q4), XP1.B17
nRDKL: DD15.15 (OE), DD16.15 (OE), DD19.11 (Y4)
nRDROM: DD41.20 (CE), R61.2 (b), XP1.A24
nRESET: C31.1 (a), DD44.26 (RESET), R42.2 (b), SB1.1, VD5.2 (A), XP1.B27
nRFSH: DD18.9 (A3), DD44.28 (RFSH)
nVF: DD11.6 (Y2), DD12.5 (B2), DD19.2 (B1)
nWAIT: DD22.5 (Q1), DD44.24 (WAIT), R22.1 (a), XP1.B20
nWE: DD22.9 (Q2), R29.1 (a)
nWR: DD29.2 (B1), DD48.6 (Q2), XP1.B18
nWRBUF: DD12.4 (A2), DD13.12 (Y6), DD22.4 (PRE1)
nXPM1: DD48.2 (Q0), XP1.B23
